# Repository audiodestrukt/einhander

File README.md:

# einhander

A one-handed hardware controller for music performance and sequencing — MC-303-inspired,
simplicity-first. Two rows of four key switches under the fingers, a thumbwheel + SHIFT on
the side for the thumb, so the other hand stays free for sliders/faders.

This repo holds the **code-driven** design: a parametric enclosure (build123d) and a
fabbable PCB (tscircuit → KiCad).

## What's here

```
cad/    parametric enclosure — build123d (machine_params.py = single source of truth),
        top/bottom shells + component stand-ins, assembly + dated render log
pcb/    RP2040 USB-MIDI controller board
          index.circuit.tsx        composes the board (flat, global nets)
          modules/                 mcu (RP2040+flash+xtal+decoupling), power (USB-C+LDO)
          lib/, imports/           shared params, custom Cherry-MX footprint, JLC parts
          scripts/                 route4.sh + the 4-layer routing toolchain
          index.circuit.kicad_pcb  routed 4-layer board
          fab/                     Gerbers + drill + CPL  (einhander-gerbers.zip → upload to JLCPCB)
pcb-rerun/  the same board re-routed unattended (2026-10-01) — 0 shorts, 2 open nets;
            found the DSN mirror bug behind pcb/'s hand patches (see pcb-rerun/README.md)
```

## The board

- **RP2040**, pure **USB-MIDI** controller (class-compliant, no drivers), wired USB-C
- 8 MX key switches on direct GPIO; EC11 thumbwheel + SHIFT broken out to a header for a
  left-wall daughterboard; one WS2812 status LED; BOOTSEL/RESET
- **4-layer**: signals on outer layers, dedicated **GND + 3V3 inner planes**
- **DRC-clean**, ~91 × 68 mm

Interactive 3D model of the populated board: **`pcb/renders/einhander-pcba.glb`** (open in any glTF viewer — Blender, VS Code glTF, or https://gltf-viewer.donmccurdy.com).

### Fabricating it

Upload `pcb/fab/einhander-gerbers.zip` to [JLCPCB](https://jlcpcb.com) (select **4 layers**). For
assembly, add `pcb/fab/einhander-bom.csv` (27 SMD parts, LCSC-mapped) + `pcb/fab/einhander-cpl.csv`
(placement). MX switches, the EC11 thumbwheel, headers, and BOOT/RESET tactiles are **hand-soldered**
(listed separately in `einhander-handsolder.csv`, kept out of the assembly BOM).

**PCBWay** uses the same `einhander-gerbers.zip` + `einhander-cpl.csv`, with `einhander-bom-pcbway.csv`
(sources by manufacturer part number instead of LCSC). `make_fab.sh` emits both BOM formats. Regenerate the whole bundle with `bash pcb/scripts/make_fab.sh pcb/index.circuit.kicad_pcb einhander`.

### Regenerating

```bash
# enclosure
cd cad && python3 machine.py            # STLs + renders

# PCB (needs bun/tscircuit, KiCad 9, Freerouting v2.2.4 + JDK 25)
cd pcb && npm install
bash scripts/route4.sh                  # export → route (4-layer) → inject → DRC
```

## Status

Enclosure prototype ✅ · Routed 4-layer PCB ✅ (fab-ready) · thumb-cluster daughterboard, RP2040
firmware (TinyUSB MIDI), and an enclosure↔board fit re-sync are next.

---
Designed with [Claude Code](https://claude.com/claude-code).

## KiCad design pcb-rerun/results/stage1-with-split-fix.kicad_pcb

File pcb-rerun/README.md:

# pcb-rerun — einhander re-routed unattended (2026-10-01)

A side-by-side re-run of the PCB pipeline next to the shipped board in [`../pcb`](../pcb). Same
circuit (`index.circuit.tsx` + `modules/` are unchanged), routed with **nobody touching it**, to
measure how close the code-driven pipeline gets on its own. Write-up:
[punkfab.com/blog/einhander-reroute](https://punkfab.com/blog/einhander-reroute/).

## Result

|                              | Shipped (`../pcb`, July, hand-finished) | Unattended, raw | Unattended + `dsn_split_sides` |
|------------------------------|------|------|------|
| Shorts                       | 0    | 1    | **0** |
| Unconnected                  | 0    | 6    | **2** |
| Dangling tracks              | 2    | 3    | **0** |
| Board-specific patch scripts | 3    | —    | **0** |
| Track length                 | 1464 mm | 1461 mm | 1421 mm |
| Vias                         | 49   | 35   | 32   |

**Not fabbable yet** — two nets are open (QSPI_SCLK, one USB_DP pad). Use `../pcb` for fab.

## What was wrong

tscircuit's Specctra DSN export dedupes footprint images by name. C11 (0805, **bottom** side)
defined the shared 0805 image, so top-side C_IN / C_OUT / C_LED were handed to Freerouting as
mirrored bottom-side parts. Every short/open in the raw run was on those three parts — the
"dense LDO corner" that `../pcb/scripts/fix_ldo_planes.py` and `patch_stragglers.py` hand-patched.

## What changed vs `../pcb`

- `scripts/dsn_split_sides.py` (new, wired into `route4.sh` step 2a) — rebuilds DSN images for any
  part whose pins disagree with the KiCad pads, compared in absolute board coordinates.
- `scripts/drc_check.py` — unconnected items now count as blocking (it printed `CLEAN` with open nets).
- `scripts/board_metrics.py` (new) — track length / segments / vias / zones for a `.kicad_pcb`.
- `scripts/dsn_freeze_ses.py` — **dead end**, kept as a record: freezing the routed SES as fixed DSN
  wiring for a tail-only second pass stalls Freerouting 2.2.4.
- `index.circuit.kicad_pcb` is the unattended + fix result (= `results/stage1-with-split-fix.kicad_pcb`).
- `fab/` and `renders/` were left out — they belong to the shipped board.

All of these are also in the `pcb-layout` skill:
[punkfab/circuit-skills](https://github.com/punkfab/circuit-skills).

## Reproduce

```bash
cd pcb-rerun
npm install                                   # tscircuit CLI (node_modules not committed)
DISPLAY=:0 bash scripts/route4.sh             # ~30 s: export -> DSN prep -> freert224 -> KiCad IPC -> DRC
/usr/bin/python3 scripts/board_metrics.py index.circuit.kicad_pcb
```

Needs the same toolchain as `../pcb`: bun/tsci, Freerouting 2.2.4 + JDK 25 (`freert224`), KiCad 9
with the IPC API (`kipy`), and system python with `pcbnew`.

## results/

| file | what |
|------|------|
| `stage0-raw-autorun.kicad_pcb`, `stage0-drc.json`, `stage0-metrics.json` | unattended run before the fix |
| `stage1-with-split-fix.kicad_pcb`, `stage1-drc.json`, `stage1-metrics.json` | unattended run with `dsn_split_sides.py` |
| `shipped-metrics.json` | the same metrics for `../pcb/index.circuit.kicad_pcb` |
| `compare.jpg`, `corner.jpg` | the figures from the blog post (KiCad F.Cu/B.Cu plots) |

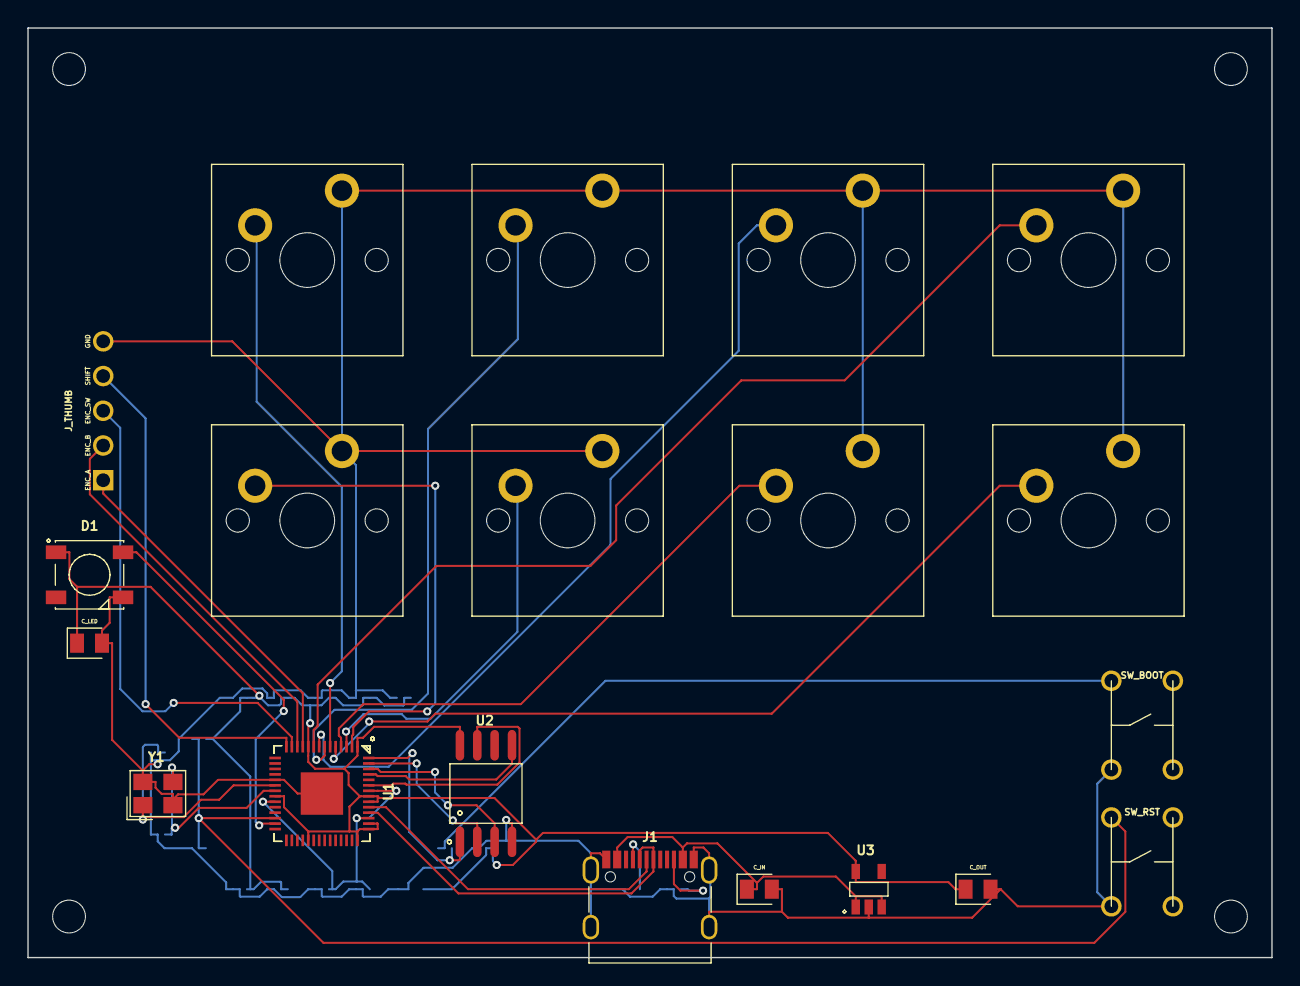
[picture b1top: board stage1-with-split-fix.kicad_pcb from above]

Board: 4 copper layers, 91.0 x 68.0 mm, 38 parts (0 on the bottom side), 31 nets.

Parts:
C1, C2, C3, C4, C5, C6, C7, C10, C14, C15: 100nF; capacitor_0402
C9: 1uF; capacitor_0402
C11: 10uF; capacitor_0805
C12, C13: 15pF; capacitor_0402
C_IN: 1uF; capacitor_0805
C_LED: 100nF; capacitor_0805
C_OUT: 1uF; capacitor_0805
D1: WS2812B_B_T
J1: TYPE_C_31_M_12
J_THUMB: J_THUMB; pin_header_pinrow5
R_BOOT: 1kΩ; resistor_res0402
R_CC1, R_CC2: 5.1kΩ; resistor_res0402
R_RUN: 10kΩ; resistor_res0402
SW1, SW2, SW3, SW4, SW5, SW6, SW7, SW8: chip
SW_BOOT: SW_BOOT; push_button_pushbutton
SW_RST: SW_RST; push_button_pushbutton
U1: RP2040
U2: W25Q16JVSSIQ
U3: AP2112K_3_3TRG1
Y1: X322512MSB4SI

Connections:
BOOT_BTN: R_BOOT.2, SW_BOOT.1
DVDD: C9.1, C10.1, U1.23, U1.45, U1.50
ENC_A: J_THUMB.1, U1.11
ENC_B: J_THUMB.2, U1.12
ENC_SW: J_THUMB.3, U1.13
GND: C1.2, C2.2, C3.2, C4.2, C5.2, C6.2, C7.2, C9.2, C10.2, C11.2, C12.2, C13.2, C14.2, C15.2, C_IN.2, C_LED.2, C_OUT.2, D1.3, J1.1, J1.2, J1.3, J1.4, J1.13, J1.14, J_THUMB.5, R_CC1.2, R_CC2.2, SW1.2, SW2.2, SW3.2, SW4.2, SW5.2, SW6.2, SW7.2, SW8.2, SW_BOOT.2, SW_RST.2, U1.19, U1.57, U2.4, U3.2, Y1.2, Y1.4
J1.A5 to R_CC1.pin1: J1.6, R_CC1.1
J1.B5 to R_CC2.pin1: J1.12, R_CC2.1
KEY0: SW1.1, U1.2
KEY1: SW2.1, U1.3
KEY2: SW3.1, U1.4
KEY3: SW4.1, U1.5
KEY4: SW5.1, U1.6
KEY5: SW6.1, U1.7
KEY6: SW7.1, U1.8
KEY7: SW8.1, U1.9
LED_DIN: D1.4, U1.27
QSPI_SCLK: U1.52, U2.6
QSPI_SD0: U1.53, U2.5
QSPI_SD1: U1.55, U2.2
QSPI_SD2: U1.54, U2.3
QSPI_SD3: U1.51, U2.7
QSPI_SS: R_BOOT.1, U1.56, U2.1
RUN: C14.1, R_RUN.2, SW_RST.1, U1.26
SHIFT: J_THUMB.4, U1.14
USB_DM: J1.7, J1.9, U1.46
USB_DP: J1.8, J1.10, U1.47
V3V3: C1.1, C2.1, C3.1, C4.1, C5.1, C6.1, C7.1, C11.1, C15.1, C_LED.1, C_OUT.1, D1.1, R_RUN.1, U1.1, U1.10, U1.22, U1.33, U1.42, U1.43, U1.44, U1.48, U1.49, U2.8, U3.5
VBUS: C_IN.1, J1.15, J1.16, U3.1, U3.3
XIN: C12.1, U1.20, Y1.1
XOUT: C13.1, U1.21, Y1.3
